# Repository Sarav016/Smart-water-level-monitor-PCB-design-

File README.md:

# Smart-water-level-monitor-PCB-design-

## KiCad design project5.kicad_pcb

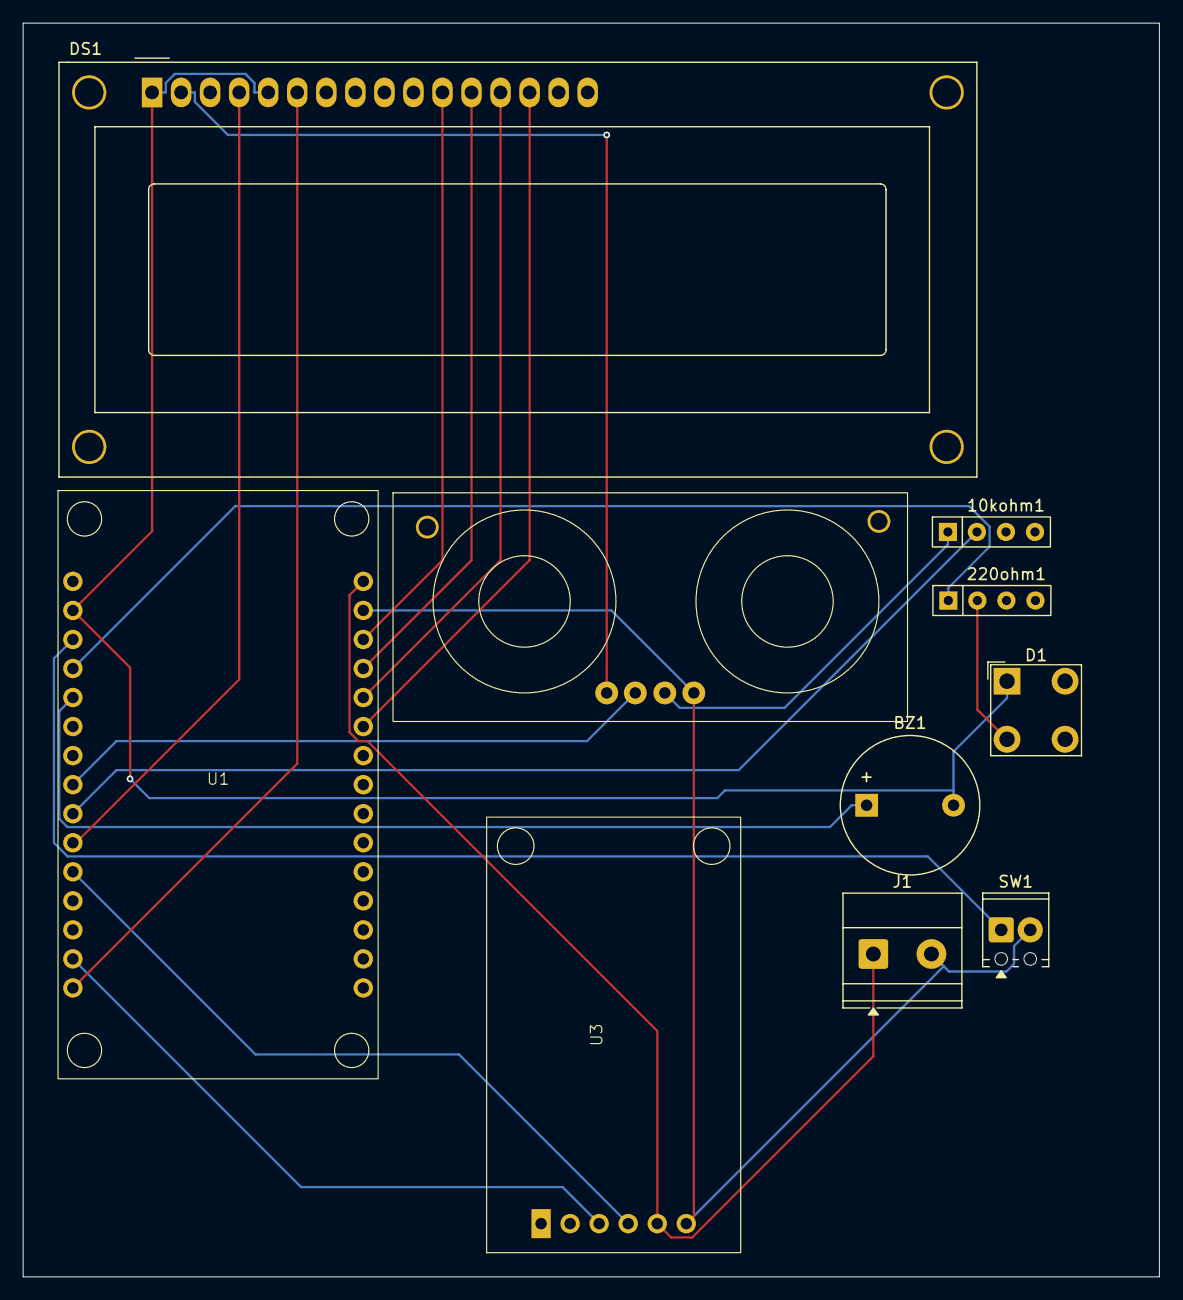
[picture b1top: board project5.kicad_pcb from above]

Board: 2 copper layers, 99.4 x 109.7 mm, 10 parts (0 on the bottom side), 19 nets.

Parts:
10kohm1, 220ohm1: R; R_Array_SIP4
BZ1: Buzzer; Buzzer_12x9.5RM7.6
D1: LED; LED_BL-FL7680RGB
DS1: WC1602A
J1: Screw_Terminal_01x02; TerminalBlock_Phoenix_MKDS-1,5-2-5.08_1x02_P5.08mm_Horizont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
SW1: SW_Push; TerminalBlock_Phoenix_MPT-0,5-2-2.54_1x02_P2.54mm_Horizontal
U1: esp32 devkit footprint
U2: ultrasonic sensor
U3: DS3231 RTC real print

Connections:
+5V: DS1.2 (VDD), U2.1 (Vcc)
GND: J1.2, SW1.2, U1.17 (gnd), U2.4 (gnd), U3.6 (gnd)
unnamed: BZ1.1 (+), U1.5 (D4/GPIO4)
unnamed: BZ1.2 (-), D1.1 (K), DS1.1 (VSS), DS1.5 (R/W), U1.2 (gnd)
unnamed: 220ohm1.2, D1.2 (A)
unnamed: DS1.11 (D4), U1.18 (D13/GPIO13)
unnamed: DS1.12 (D5), U1.19 (D12/GPIO12)
unnamed: DS1.13 (D6), U1.20 (D14/GPIO14)
unnamed: DS1.14 (D7), U1.21 (D27/GPIO27)
unnamed: DS1.6 (E), U1.15 (D23/GPIO23)
unnamed: DS1.4 (RS), U1.10 (D19/GPIO19)
unnamed: J1.1, U1.16 (5v), U3.5 (Vcc)
unnamed: 220ohm1.1, U1.4 (D2/GPIO2)
unnamed: U1.8 (D5/GPIO5), U2.2 (TRIG)
unnamed: SW1.1, U1.3 (D15/GPIO15)
unnamed: 10kohm1.2, U1.9 (D18/GPIO18)
unnamed: U1.11 (D21/GPIO21), U3.4 (SDA)
unnamed: U1.14 (D22/GPIO22), U3.3 (SCL)
unnamed: 10kohm1.1, U2.3 (ECHO)
